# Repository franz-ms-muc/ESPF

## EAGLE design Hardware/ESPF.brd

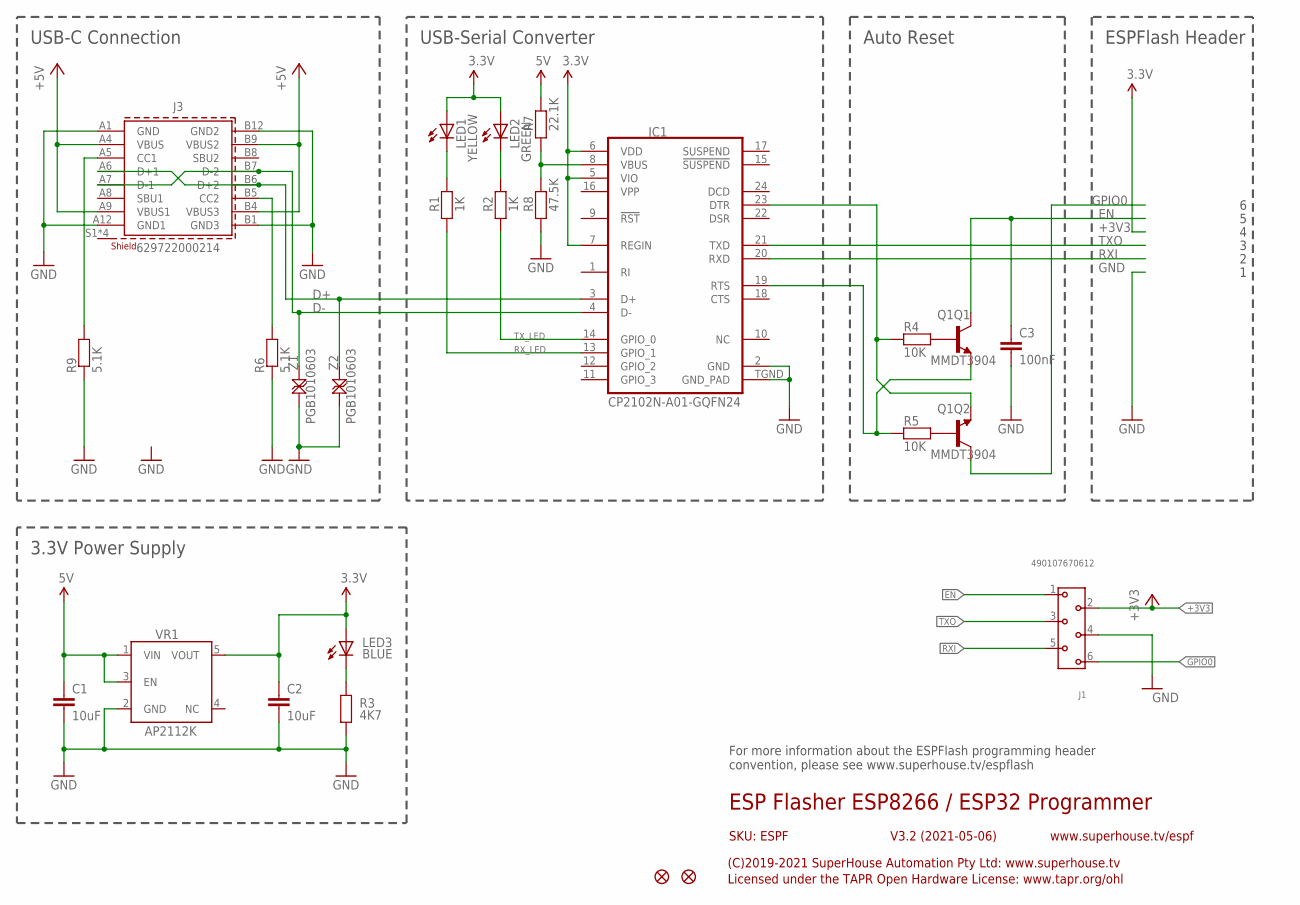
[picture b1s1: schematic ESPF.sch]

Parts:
C1, C2: 10uF; C0603
C3: 100nF; C0603
FID1, FID2: FIDUCIAL1X2.5; FIDUCIAL-1X2.5
IC1: CP2102N-A01-GQFN24; QFN-24
J1: 490107670612; 490107670612_DEBUGGING
J3: 629722000214
LED1: YELLOW; LED-0603
LED2: GREEN; LED-0603
LED3: BLUE; LED-0603
Q1: MMDT3904; SOT-363
R1, R2: 1K; R0603
R3: 4K7; R0603
R4, R5: 10K; R0603
R6, R9: 5.1K; R0603
R7: 22.1K; R0603
R8: 47.5K; R0603
VR1: AP2112K-3.3; SOT23-5
Z1, Z2: PGB1010603; TVS0603

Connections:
+3V3: C2.1, IC1.5 (VIO), IC1.6 (VDD), IC1.7 (REGIN), J1.2, LED1.A, LED2.A, LED3.A, VR1.5 (VOUT)
+5V: C1.1, J3.A4 (VBUS), J3.A9 (VBUS1), J3.B4 (VBUS3), J3.B9 (VBUS2), R7.2, VR1.1 (VIN), VR1.3 (EN)
D+: IC1.3 (D+), J3.A6 (D+1), J3.B6 (D+2), Z2.2
D-: IC1.4 (D-), J3.A7 (D-1), J3.B7 (D-2), Z1.2
DTR: IC1.23 (DTR), Q1.1 (E), R4.1
EN: C3.1, J1.1, Q1.3 (C)
GND: C1.2, C2.2, C3.2, IC1.2 (GND), IC1.TGND (GND_PAD), J1.4, J3.A1 (GND), J3.A12 (GND1), J3.B1 (GND3), J3.B12 (GND2), R3.1, R6.1, R8.1, R9.1, VR1.2 (GND), Z1.1, Z2.1
GPIO0: J1.6, Q1.6 (C)
unnamed: LED1.C, R1.2
unnamed: LED2.C, R2.2
unnamed: LED3.C, R3.2
unnamed: IC1.8 (VBUS), R7.1, R8.2
unnamed: Q1.5 (B), R4.2
unnamed: Q1.2 (B), R5.2
unnamed: J3.B5 (CC2), R6.2
unnamed: J3.A5 (CC1), R9.2
RTS: IC1.19 (RTS), Q1.4 (E), R5.1
RXI: IC1.20 (RXD), J1.5
RX_LED: IC1.13 (GPIO_1), R1.1
TXO: IC1.21 (TXD), J1.3
TX_LED: IC1.14 (GPIO_0), R2.1

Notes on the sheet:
ESP Flasher ESP8266 / ESP32 Programmer
V3.2 (2021-05-06)
SKU: ESPF
(C)2019-2021 SuperHouse Automation Pty Ltd: www.superhouse.tv
Licensed under the TAPR Open Hardware License: www.tapr.org/ohl
www.superhouse.tv/espf
USB-C Connection
USB-Serial Converter
Auto Reset
ESPFlash Header
3.3V Power Supply
For more information about the ESPFlash programming header convention, please see www.superhouse.tv/espflash

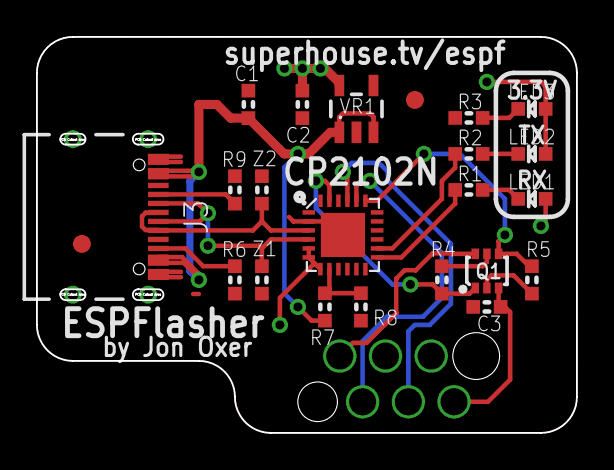
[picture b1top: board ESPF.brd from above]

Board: 2 copper layers, 30.0 x 22.0 mm, 24 parts (1 on the bottom side), 21 nets.

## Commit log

2023-04-14 gitignore
2023-04-14 Wurth_Connectors_WR-USB
2023-04-14 With Würht Connectors.

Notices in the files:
parts and their libraries:
Wurth_Connectors_WR-USB: Copyright: Würth Elektronik
